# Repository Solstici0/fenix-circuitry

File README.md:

# fenix-circuitry
Improving Planeta Fenix productive process

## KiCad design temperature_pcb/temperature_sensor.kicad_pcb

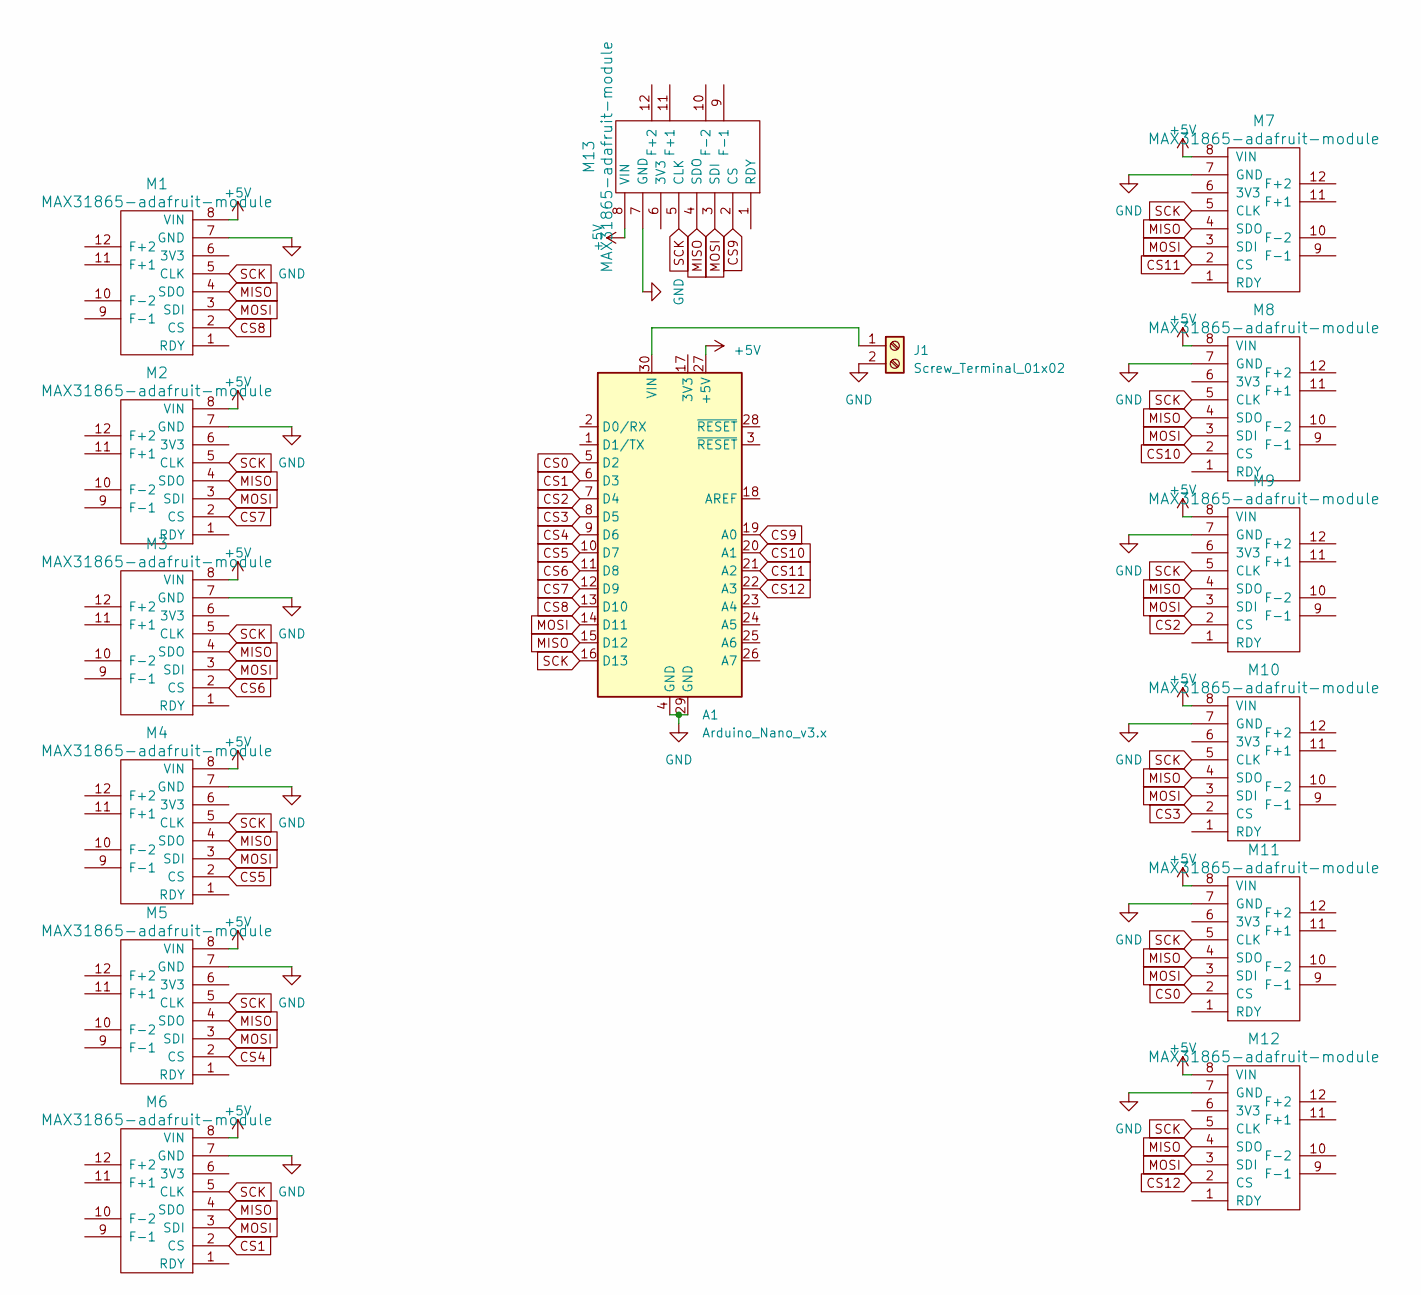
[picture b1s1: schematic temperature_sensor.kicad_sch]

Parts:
A1: Arduino_Nano_v3.x; Arduino_Nano
J1: Screw_Terminal_01x02; TerminalBlock_bornier-2_P5.08mm
M1, M2, M3, M4, M5, M6, M7, M8, M9, M10, M11, M12, M13: MAX31865-adafruit-module; MAX31865-module-Adafruit

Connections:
+5V: A1.27 (+5V), M1.8 (VIN), M2.8 (VIN), M3.8 (VIN), M4.8 (VIN), M5.8 (VIN), M6.8 (VIN), M7.8 (VIN), M8.8 (VIN), M9.8 (VIN), M10.8 (VIN), M11.8 (VIN), M12.8 (VIN), M13.8 (VIN)
CS0: A1.5 (D2), M11.2 (CS)
CS1: A1.6 (D3), M6.2 (CS)
CS2: A1.7 (D4), M9.2 (CS)
CS3: A1.8 (D5), M10.2 (CS)
CS4: A1.9 (D6), M5.2 (CS)
CS5: A1.10 (D7), M4.2 (CS)
CS6: A1.11 (D8), M3.2 (CS)
CS7: A1.12 (D9), M2.2 (CS)
CS8: A1.13 (D10), M1.2 (CS)
CS9: A1.19 (A0), M13.2 (CS)
CS10: A1.20 (A1), M8.2 (CS)
CS11: A1.21 (A2), M7.2 (CS)
CS12: A1.22 (A3), M12.2 (CS)
GND: A1.4 (GND), A1.29 (GND), J1.2, M1.7 (GND), M2.7 (GND), M3.7 (GND), M4.7 (GND), M5.7 (GND), M6.7 (GND), M7.7 (GND), M8.7 (GND), M9.7 (GND), M10.7 (GND), M11.7 (GND), M12.7 (GND), M13.7 (GND)
MISO: A1.15 (D12), M1.4 (SDO), M2.4 (SDO), M3.4 (SDO), M4.4 (SDO), M5.4 (SDO), M6.4 (SDO), M7.4 (SDO), M8.4 (SDO), M9.4 (SDO), M10.4 (SDO), M11.4 (SDO), M12.4 (SDO), M13.4 (SDO)
MOSI: A1.14 (D11), M1.3 (SDI), M2.3 (SDI), M3.3 (SDI), M4.3 (SDI), M5.3 (SDI), M6.3 (SDI), M7.3 (SDI), M8.3 (SDI), M9.3 (SDI), M10.3 (SDI), M11.3 (SDI), M12.3 (SDI), M13.3 (SDI)
unnamed: A1.30 (VIN), J1.1
SCK: A1.16 (D13), M1.5 (CLK), M2.5 (CLK), M3.5 (CLK), M4.5 (CLK), M5.5 (CLK), M6.5 (CLK), M7.5 (CLK), M8.5 (CLK), M9.5 (CLK), M10.5 (CLK), M11.5 (CLK), M12.5 (CLK), M13.5 (CLK)

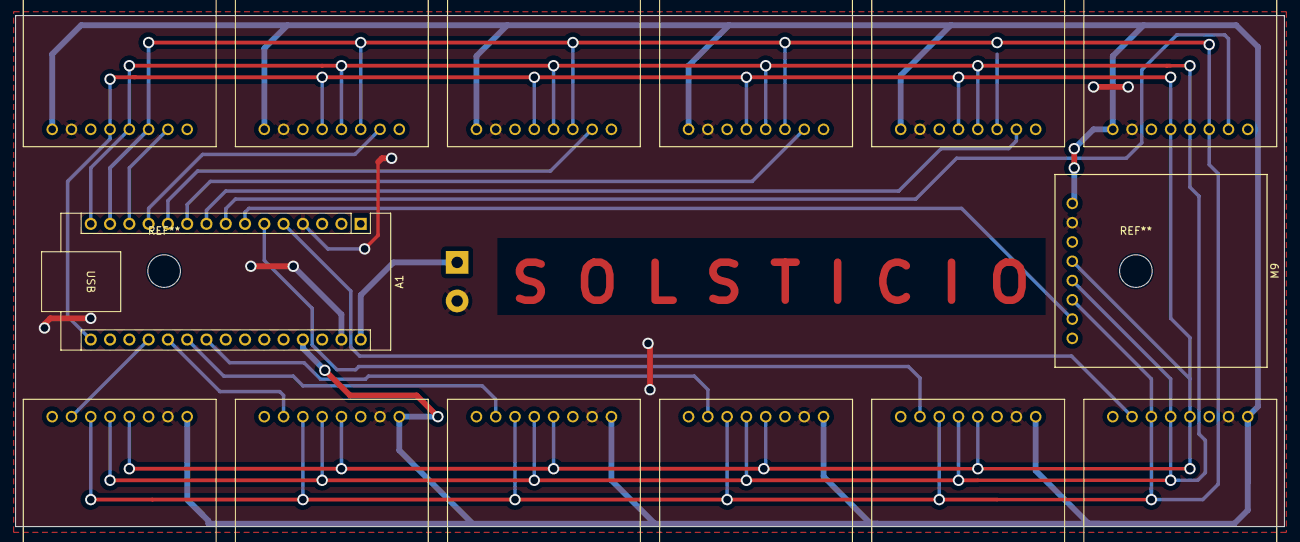
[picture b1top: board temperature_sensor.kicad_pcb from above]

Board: 2 copper layers, 167.1 x 67.3 mm, 15 parts (1 on the bottom side), 19 nets.

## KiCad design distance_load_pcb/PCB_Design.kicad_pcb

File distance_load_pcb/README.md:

# fenix-circuitry
Improving Planeta Fenix productive process

## Interesting Links

- [Relate schematic and footprint pins](https://forum.kicad.info/t/how-does-kicad-know-which-symbol-pin-represents-which-pad-of-the-footprint/11889)

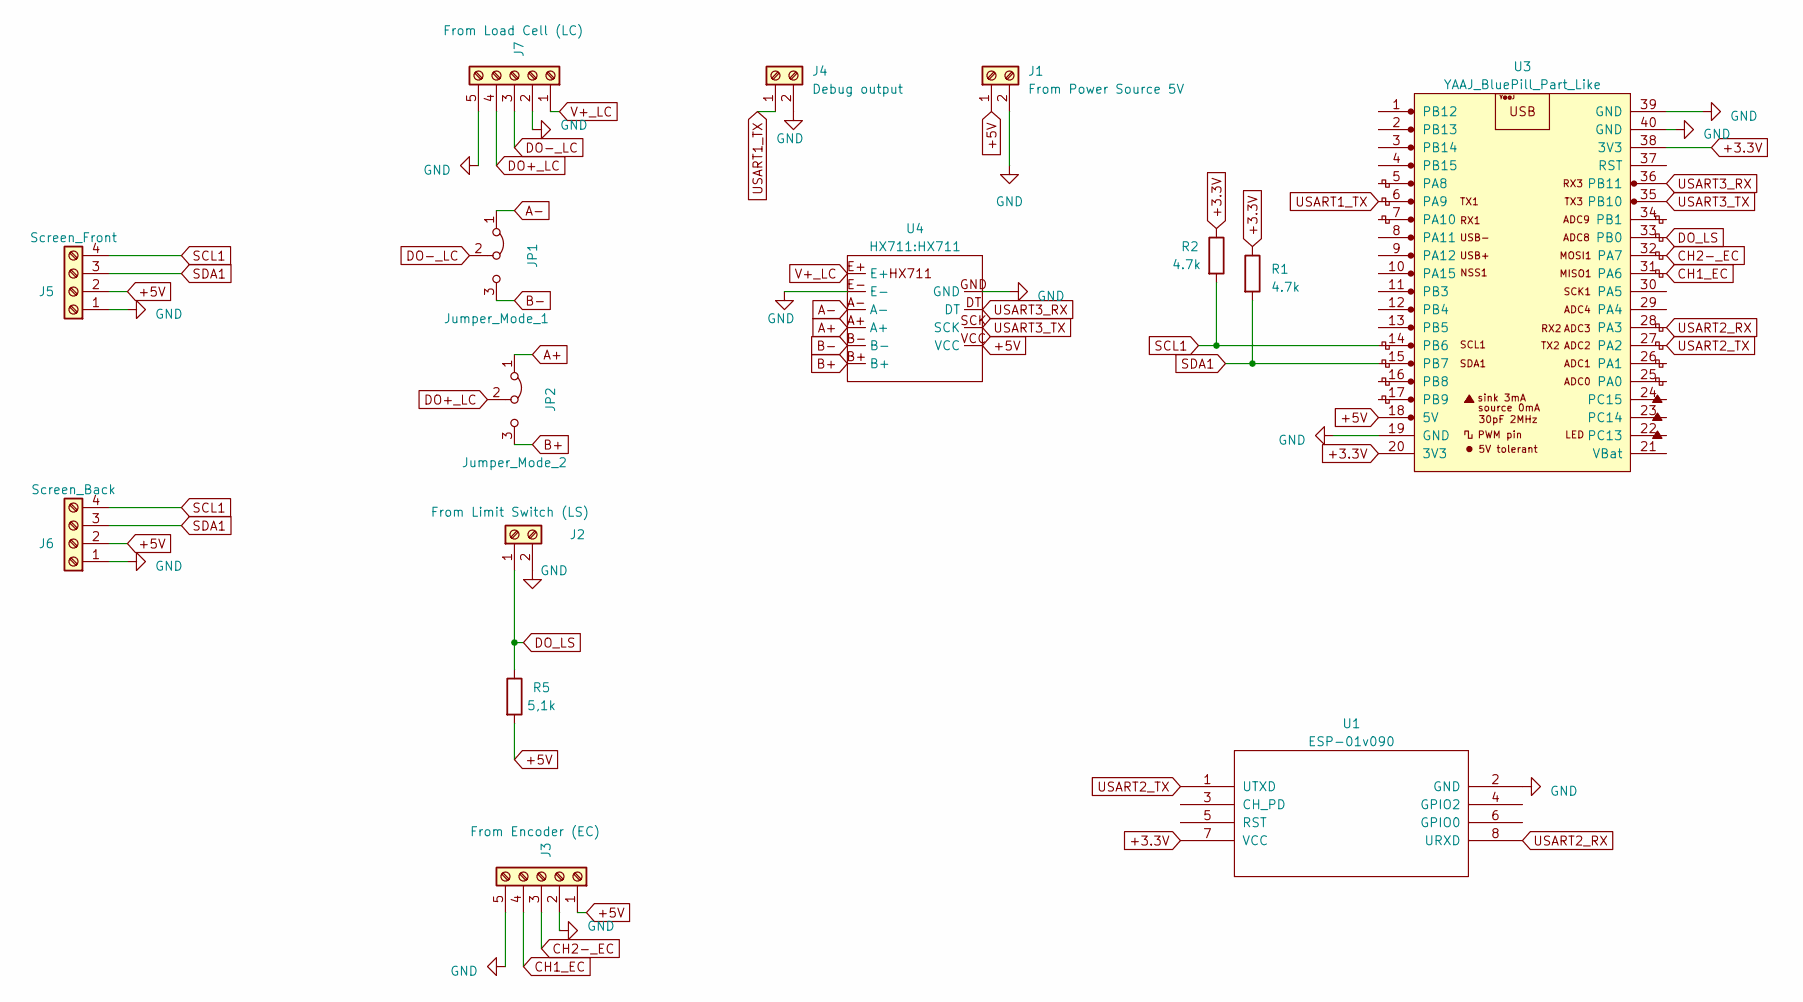
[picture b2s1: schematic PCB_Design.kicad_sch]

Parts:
J1: From Power Source 5V; TerminalBlock_TE_282834-2_1x02_P2.54mm_Horizontal
J2: From Limit Switch (LS); TerminalBlock_TE_282834-2_1x02_P2.54mm_Horizontal
J3: From Encoder (EC); TerminalBlock_TE_282834-5_1x05_P2.54mm_Horizontal
J4: Debug output; TerminalBlock_TE_282834-2_1x02_P2.54mm_Horizontal
J5: Screen_Front; TerminalBlock_TE_282834-4_1x04_P2.54mm_Horizontal
J6: Screen_Back; TerminalBlock_TE_282834-4_1x04_P2.54mm_Horizontal
J7: From Load Cell (LC); TerminalBlock_TE_282834-5_1x05_P2.54mm_Horizontal
JP1: Jumper_Mode_1; PinHeader_1x03_P2.54mm_Vertical
JP2: Jumper_Mode_2; PinHeader_1x03_P2.54mm_Vertical
R1, R2: 4.7k; R_Axial_DIN0207_L6.3mm_D2.5mm_P10.16mm_Horizontal
R5: 5,1k; R_Axial_DIN0207_L6.3mm_D2.5mm_P10.16mm_Horizontal
U1: ESP-01v090; ESP-01
U3: YAAJ_BluePill_Part_Like; YAAJ_BluePill_1
U4: HX711

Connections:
+3.3V: R1.1, R2.1, U1.7 (VCC), U3.20 (3V3), U3.38 (3V3)
+5V: J1.1, J3.1, J5.2, J6.2, R5.2, U3.18 (5V), U4.VCC
A+: JP2.1 (A), U4.A+
A-: JP1.1 (A), U4.A-
B+: JP2.3 (B), U4.B+
B-: JP1.3 (B), U4.B-
CH1_EC: J3.4, U3.31 (PA6)
CH2-_EC: J3.3, U3.32 (PA7)
DO+_LC: J7.4, JP2.2 (C)
DO-_LC: J7.3, JP1.2 (C)
DO_LS: J2.1, R5.1, U3.33 (PB0)
GND: J1.2, J2.2, J3.2, J3.5, J4.2, J5.1, J6.1, J7.2, J7.5, U1.2 (GND), U3.19 (GND), U3.39 (GND), U3.40 (GND), U4.E-, U4.GND
SCL1: J5.4, J6.4, R2.2, U3.14 (PB6)
SDA1: J5.3, J6.3, R1.2, U3.15 (PB7)
USART1_TX: J4.1, U3.6 (PA9)
USART2_RX: U1.8 (URXD), U3.28 (PA3)
USART2_TX: U1.1 (UTXD), U3.27 (PA2)
USART3_RX: U3.36 (PB11), U4.DT
USART3_TX: U3.35 (PB10), U4.SCK
V+_LC: J7.1, U4.E+

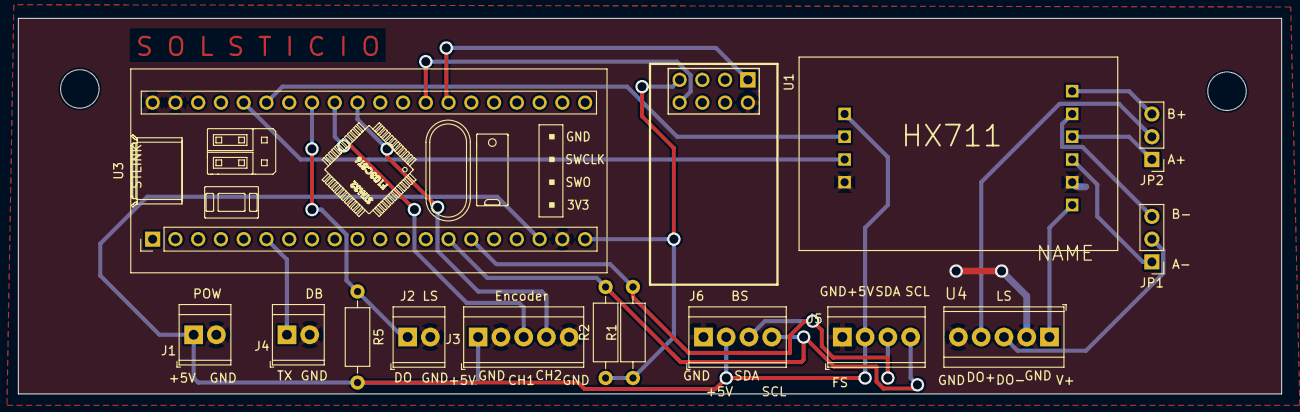
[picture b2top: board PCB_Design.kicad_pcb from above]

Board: 2 copper layers, 141.0 x 41.9 mm, 15 parts (0 on the bottom side), 20 nets.

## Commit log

2023-04-27 Screen, LS, Encoder, Load Cell, power sources (15 and 5 V), STM32 added
2023-04-28 Sensor module added
2023-04-28 separate 3 folders for each pcb
2023-04-28 first version of sensor bed layout
2023-05-02 first version of the pcb for the temperature sensors
2023-05-02 removed unused pins
2023-05-02 add STM32 blue/blackpill Footprint and schematic
2023-05-02 add PCB footprint force and distance module[D
2023-05-03 Add pin names
2023-05-03 Fixed problems, working on footprint tracks and pads
2023-05-04 finish pcb force and distance
2023-05-04 felipin's suggestions, all the tracs arrive at the components by the bottom
2023-05-04 fix pcb
2023-05-09 fixed max31865 footprint pinout, unrouted all the max in the temperature_sensor pcb
2023-05-09 solid gnd plane, added solsticio to the side
2023-05-10 Vamos Solsticio!
2023-05-16 last revision of the distance_load, printed
2023-05-16 routed new pads
